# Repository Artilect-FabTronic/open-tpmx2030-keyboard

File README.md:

# open-tpmx2030-keyboard

Bienvenue sur le dépôt du projet de clavier BEPO `open-tpmx2030-keyboard` du FabLab Artilect.

Inspirée par la [présentation du projet ToucheLibre faite par Lilian Tribouilloy le 9 mars 2020 au fablab Artilect](https://touchelibre.fr/index.php/presentation-projet-en-video/) de Toulouse pendant l’une des soirées SuperLundi.

Ce projet a pour objectif de concevoir un clavier mécanique open source simple, basé sur le modèle de [clavier TypeMatrix 2030](https://typematrix.com/fr/products/2030/), avec des touches Cherry MX2A et des keycaps personnalisables.

Pour plus de détails sur la disposition bépo, veuillez consulter le wiki : <https://bepo.fr/wiki/TypeMatrix>

---

## Contribuer au projet

Afin de permettre à chacun de contribuer à la version 1.0.0 du clavier `open-tpmx2030-keyboard`, merci de respecter la règle de nommage des branches et de ne pas commiter directement sur la branche main. En effet, la branche main est protégée et toute contribution doit passer par une pull request.

Un grand merci à tous les futurs contributeurs qui participeront à ce projet et qui continueront à le faire évoluer.

---

## Organisation du projet

Le présent fichier `README.md` est le point d'entrée du projet.

Le projet est structuré en différentes branches de la manière suivante :

- `feature/pcb` : contient les fichiers de conception du PCB du clavier.
- `feature/firmware` : contient le firmware du clavier.

Le dossier [`*/docs/`](./docs/README.md) : contient la documentation du projet.

Voir les bonnes pratiques pour les messages de commit : <https://commitizen-tools.github.io/commitizen/tutorials/writing_commits/>

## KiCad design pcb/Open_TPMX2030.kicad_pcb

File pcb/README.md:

# 🛠️ Guide de Conception KiCad — Projet Open-TPMX2030

Ce guide est destiné aux membres et hackers du FabLab Artilect participant au développement de la carte électronique (PCB) du clavier ergonomique Open-TPMX2030.

Il regroupe les règles de l'art en ingénierie électronique pour concevoir un PCB propre, robuste, facile à fabriquer (JLCPCB / PCBWay) et à déboguer.

---

## 📌 1. Structure du Projet & Conventions de Nommage

Editer le fichier `.kicad_pro` avec un éditeur de texte est modifier la section `text_variables` en fin du fichier avec les éléments suivants :

```plaintext
  "text_variables": {
    "COMPANY": "Copyright (c) 2026 Artilect FabLab Toulouse",
    "CREATION_DATE": "2026-08-16",
    "LICENSE": "Apache-2.0 license",
    "PROJECT_NAME": "Open-TPMX2030 keyboard",
    "REVISION": "1.0.0",
    "SERIAL_NUM": "S/N: 260816-Artilect-P001",
    "USER_EMAIL": "arnauld.biganzoli@gmail.com",
    "USER_NAME": "ArnauldDev"
  },
```

Et depuis l'édition des fichiers `.kicad_sch` et `.kicad_pcb`, compléter la section `title_block` avec les éléments suivants :

```plaintext
	(title_block
		(title "${PROJECT_NAME}")
		(date "${CREATION_DATE}")
		(rev "${REVISION}")
		(company "${COMPANY}")
		(comment 1 "License: ${LICENSE}")
		(comment 2 "${USER_EMAIL}")
		(comment 3 "${USER_NAME}")
		(comment 4 "Electrical CAD Operator:")
	)
```

### 1.1 Organisation du Dépôt Git

Tout le projet Hardware réside dans le dossier `/pcb` du dépôt GitHub `open-tpmx2030-keyboard`.

```plaintext
├── pcb/
│   ├── open_tpmx2030.kicad_pro       # Fichier projet KiCad
│   ├── open_tpmx2030.kicad_sch       # Schématique racine (Feuille Principale)
│   ├── open_tpmx2030.kicad_pcb       # Layout du PCB
│   ├── open_tpmx2030.kicad_dru       # Règles de routage personnalisées (DRC)
│   ├── mcu_rp2040.kicad_sch          # Module Microcontrôleur RP2040-Zero
│   ├── matrix_expanders.kicad_sch    # Module MCP23017 (I2C)
│   ├── key_matrix.kicad_sch          # Matrice de switches (keyboard 102 touches + diodes)
│   ├── user_interface.kicad_sch      # Encodeurs + LEDs
│   └── libraries/                    # Symboles et Empreintes spécifiques
│       ├── symbols/                  # .kicad_sym (.kicad_sym)
│       ├── footprints/               # .kicad_mod (.pretty)
│       └── 3dmodels/                 # Modèles 3D (.3dshapes, .stp)
└── manufacturing/                    # Gerbers, Drill, BOM, CPL (Générés)
```

### 1.2 Règles de nommage des composants

Pour s'y retrouver facilement lors du soudage manuel ou de l'inspection :

* U1, U2, ... : Circuits intégrés (RP2040, MCP23017)
* SW1 à SW102 : Switches de touches (Cherry MX2A)
* SW_ENC1 à SW_ENC3 : Switches d'encodeurs rotatifs
* D1 à D102 : Diodes de matrice (1N4148 / SOD-123)
* LED1 à LED4 : LEDs d'état (0805)
* R1, R2, ... : Résistances
* C1, C2, ... : Condensateurs
* ENC1 à ENC3 : Encodeurs rotatifs (EC11)

---

## 📐 2. La schématique (Eeschema)

### 2.1 Approche par Schémas Hiérarchiques

Ne mettez jamais l'intégralité d'un projet de 102 touches sur une seule page géante !

Utilisez des Feuilles Hiérarchiques (Hierarchical Sheets) :

1. Racine (open_tpmx2030.kicad_sch) : Bloc-diagramme reliant les sous-modules via des labels hiérarchiques (Bus I2C, INT, Power).
2. Feuille mcu_rp2040 : RP2040-Zero, régulateur de tension (si besoin), filtrage d'alimentation, connecteur USB-C.
3. Feuille matrix_expanders : Les 2x MCP23017, adresses I2C (A0, A1, A2), résistances de tirage I2C (Pull-up).
4. Feuille key_matrix : Matrice $8 \times 13$ réparties proprement en sous-ensembles (ex: réplication de blocs).
5. Feuille user_interface : 3 Encodeurs EC11 + 4 LEDs.

### 2.2 Bonnes Pratiques de Schématique

* **Sens de lecture :** Les signaux d'entrée viennent de la **gauche**, les sorties vont vers la **droite**, les alimentations ($V_{CC}$ / $+3.3\text{V}$) sont en **haut**, et les masses ($\text{GND}$) sont en **bas**.
* **Condensateurs de découplage :** Dessinez TOUJOURS les condensateurs de découplage ($100\text{ nF}$) à côté des broches d'alimentation des puces correspondantes (`VCC/VDD` du MCP23017, etc.) sur le schéma, pour rappeler qu'ils doivent être soudés au plus près en layout.
* **Net Labels clairs :** Utilisez des noms de réseaux explicites (`I2C_SDA`, `I2C_SCL`, `ROW_0`, `COL_12`, `ENC_VOL_CLK`).

---

## ⚡ 3. Les Règles de Routage PCB (Pcbnew)

### 3.1 Empilement de la Carte (Layer Stackup - 2 Couches)

Puisqu'il s'agit d'une carte 2 couches classique (1.6 mm FR4, $35\ \mu\text{m}$ Cuivre) :

* Couche Supérieure (F.Cu - Red) : Signaux principaux, bus de données, matrice de touches.
* Couche Inférieure (B.Cu - Blue) : Plan de Masse Continu ($\text{GND}$).
  * _Règle absolue :_ Évitez au maximum de couper le plan de masse face inférieure avec de longues pistes. Si une piste doit passer en `B.Cu`, faites un "pont" court et revenez en `F.Cu`.

### 3.2 Largeur de Pistes (Track Widths)

Configurons les classes de réseaux (Net Classes) dans KiCad :

| Classe de Réseau | Largeur de Piste                   | Isolation (Clearance)              | Via (Perçage / Anneau)          | Usage                           |
| ---------------- | ---------------------------------- | ---------------------------------- | ------------------------------- | ------------------------------- |
| Default          | $0.20\text{ mm}$ ($8\text{ mil}$)  | $0.20\text{ mm}$ ($8\text{ mil}$)  | $0.6\text{ mm} / 0.3\text{ mm}$ | Signaux matrice, LEDs, GPIOs    |
| HighSpeed_I2C    | $0.25\text{ mm}$ ($10\text{ mil}$) | $0.25\text{ mm}$ ($10\text{ mil}$) | $0.6\text{ mm} / 0.3\text{ mm}$ | Bus I2C (SDA / SCL à 1 MHz)     |
| Power (+3.3V)    | $0.50\text{ mm}$ ($20\text{ mil}$) | $0.25\text{ mm}$ ($10\text{ mil}$) | $0.8\text{ mm} / 0.4\text{ mm}$ | Lignes d'alimentation principal |
| Power (+5V USB)  | $0.75\text{ mm}$ ($30\text{ mil}$) | $0.30\text{ mm}$ ($12\text{ mil}$) | $0.8\text{ mm} / 0.4\text{ mm}$ | VBUS d'entrée USB               |

### 3.3 Placement des Composants

1. **Positionnement Ergonomique (Fixe) :** Placez d'abord les switches MX2A (espacement standard $19.05\text{ mm} \times 19.05\text{ mm}$ ou selon le layout spécifique TypeMatrix), les 3 encodeurs et les 4 LEDs.
2. **Zone Microcontrôleur & Expanders :** Placez le RP2040-Zero et les 2x MCP23017 dans la partie supérieure de la carte.
3. **Condensateurs de découplage ($100\text{ nF}$) :** Placer IMPÉRATIVEMENT chaque condensateur de découplage à moins de $2\text{ mm}$ de la broche $V_{DD}$ du MCP23017, relié directement au plan de masse par un via.

---

## 🛡️ 4. Intégrité du Signal & Compatibilité Électromagnétique (CEM)

1. **Bus I2C à 1 MHz :**
  * Gardez les pistes I2C_SDA et I2C_SCL parallèles, de longueur similaire et le plus court possible entre le RP2040-Zero et les deux MCP23017.
  * Placez les résistances de tirage ($R_{pullup} = 2.2\text{ k}\Omega$) près du RP2040-Zero.
2. **Diodes Anti-Ghosting :**
  * Chaque touche contient une diode 1N4148 (boîtier SOD-123). Placez la diode juste à côté du pad du switch correspondant pour garder un routage ultra-propre et compact.
3. **Vias de Masse (Via Stitching) :**
  * Distribuez généreusement des vias de masse autour du microcontrôleur et le long du contour de la carte pour assurer une excellente continuité du plan de masse GND.

---

## 🔍 5. Liste de Contrôle Avant Fabrication (Checklist DRC)

Avant de générer les fichiers Gerber pour le FabLab ou l'usine :

- [ ] Lancer le DRC (Design Rules Check) : 0 erreur, 0 avertissement toléré.
- [ ] Contrôle d'empreintes (Footprints) : Vérifier le sens des diodes (Cathode / Anode) et l'orientation du RP2040-Zero.
- [ ] Trous de Fixation (Mounting Holes) : Placer des trous $M3$ (non métallisés ou reliés à la masse) aux 4 coins et au centre pour la rigidité lors de la frappe.
- [ ] Visualisation 3D (Alt + 3) : Vérifier qu'aucun composant ne se chevauche (notamment les corps des switches MX2A et les encodeurs EC11).
- [ ] Sérigraphie (Silkscreen) :
  * Nom du projet : Open-TPMX2030 (FabLab Artilect)
  * Version du PCB : v1.0.0 - 2026
  * Logos : Logo Open Source Hardware + Logo Artilect.
  * Indication lisible des LEDs (NUM/FN, CAPS, SCROLL, DVORAK) et des fonctions des encodeurs (LUM, MIC, VOL).

---

## 📦 6. Export pour la Fabrication

Exportez depuis KiCad dans le dossier `/production` :

1. **Fichiers Gerber (RS-274X) :** Couches `F.Cu`, `B.Cu`, `F.Silkscreen`, `B.Silkscreen`, `F.Mask`, `B.Mask`, `Edge.Cuts` (Contour).
2. **Fichier de Perçage (Excellon / NC Drill) :** Unités en mm, coordonnées absolues.
3. **Fichiers de Placement SMT (Position / CPL) :** Fichier `.csv` pour l'assemblage automatique des composants de surface (Diodes SOD-123, MCP23017, Résistances 0805).

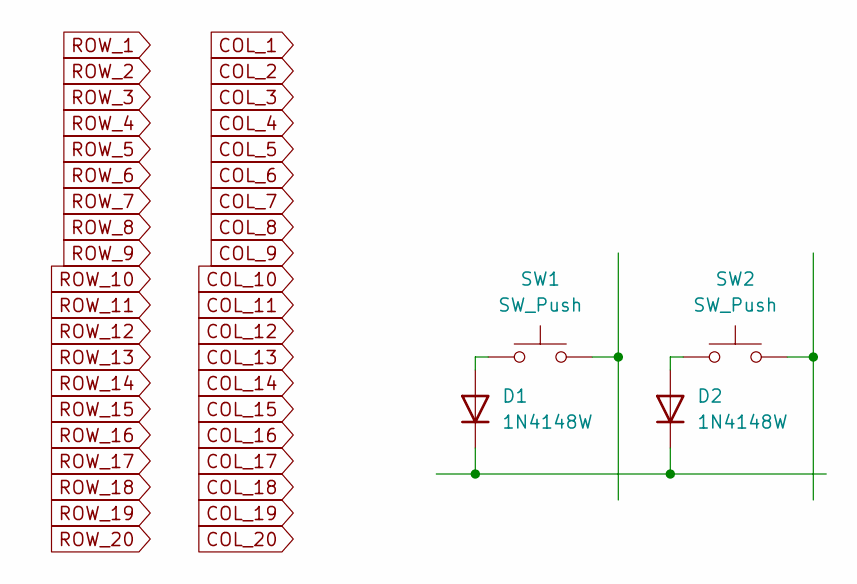
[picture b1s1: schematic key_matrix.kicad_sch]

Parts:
D1, D2: 1N4148W; D_SOD-123
SW1: SW_Push; SW_Hotswap_Kailh_Choc_V1V2_1.00u
SW2: SW_Push; SW_Hotswap_Kailh_MX_1.00u

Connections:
unnamed: D1.2 (A), SW1.1 (1_1)
unnamed: D1.1 (K), D2.1 (K)
unnamed: D2.2 (A), SW2.1 (1_1)

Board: 2 copper layers, 4 parts (0 on the bottom side), 3 nets, no tracks yet.
